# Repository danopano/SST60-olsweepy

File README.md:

# SST60-olsweepy
This repo is a fork and mod of dededecline/SST60! Below renders are from his original design.  
The provided production files cover daughterboard variants with and without flex cuts.  
Kicad 8.0 is recommended, with the JLC PCB plugin installed.  

## Fully open source multi-layout 60% PCB

<sub> renders outdated, using the old outline. </sub>

## Layout support

## Features
- RGB Underglow
- RP2040 processor
- MX and Alps compatible
- Indicator light positions for Caps Lock and Esc
- Standard tray mount support
- Gummy O-Ring support (Bakenko, ogre, etc. anything that h60 supports, this does too.)
- USB-C or Unified Daughterboard (or equivalent with the same pinout)
- Overcurrent and ESD protection
- Flex meme cuts

## ***DISCLAIMER***
Note: the below claim is not yet applicable for this fork.
This PCB has been tested and confirmed to work properly. The members of the PCB development team are not liable if you end up with a non-functional pcb. Order at your own risk. Support will not be provided but pull requests will be reviewed and possibly accepted.

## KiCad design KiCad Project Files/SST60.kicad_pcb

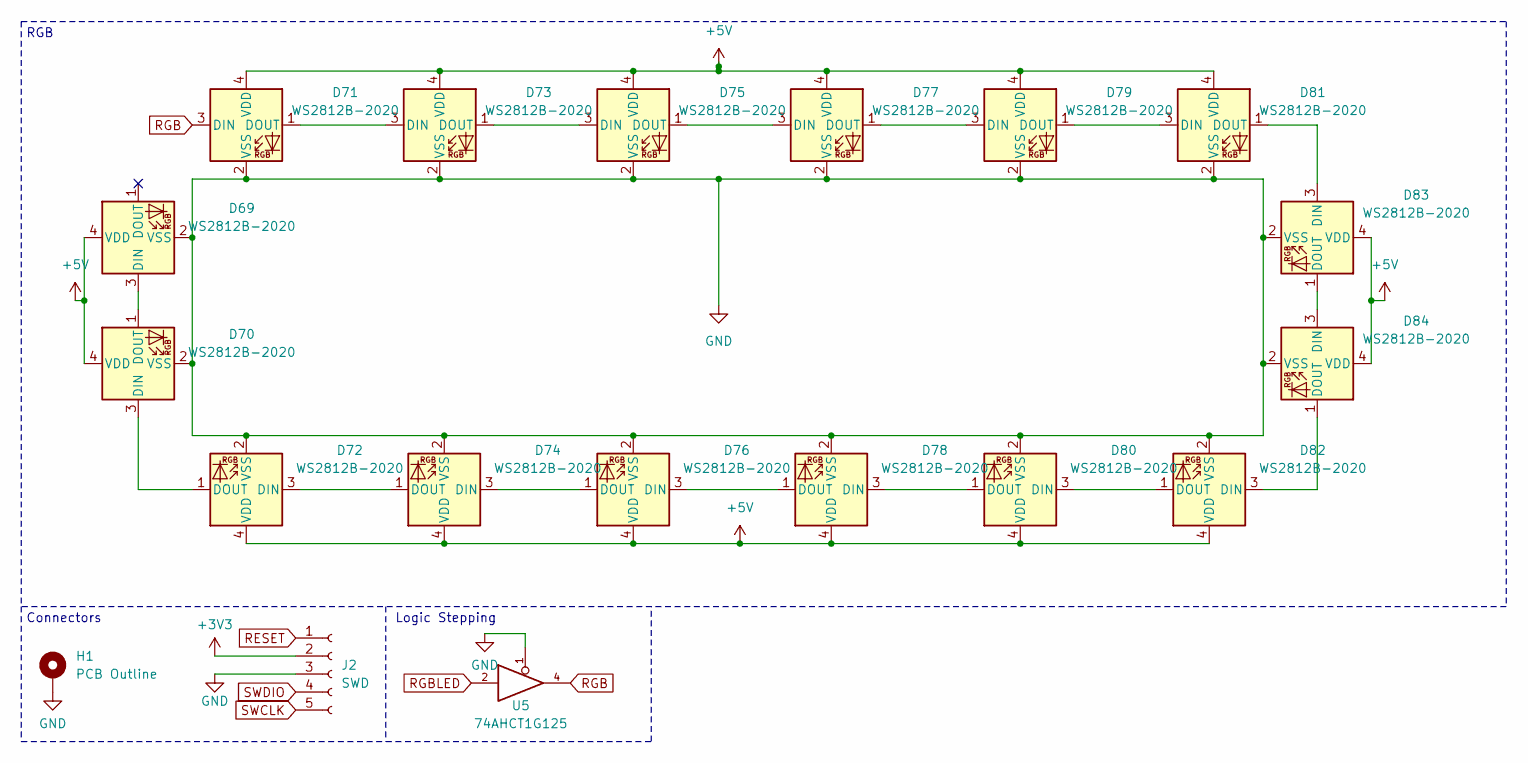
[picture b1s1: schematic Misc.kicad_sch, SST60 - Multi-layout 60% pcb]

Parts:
D69, D70, D71, D72, D73, D74, D75, D76, D77, D78, D79, D80, D81, D82, D83, D84: WS2812B-2020; LED_WS2812_2020
H1: PCB Outline; L60 Outline
J2: SWD; PinHeader_1x05_P2.54mm_Vertical
U5: 74AHCT1G125; SOT-23-5

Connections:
+3V3: J2.2; also elsewhere on the board
+5V: D69.4 (VDD), D70.4 (VDD), D71.4 (VDD), D72.4 (VDD), D73.4 (VDD), D74.4 (VDD), D75.4 (VDD), D76.4 (VDD), D77.4 (VDD), D78.4 (VDD), D79.4 (VDD), D80.4 (VDD), D81.4 (VDD), D82.4 (VDD), D83.4 (VDD), D84.4 (VDD), U5.5 (+5V); also elsewhere on the board
GND: D69.2 (VSS), D70.2 (VSS), D71.2 (VSS), D72.2 (VSS), D73.2 (VSS), D74.2 (VSS), D75.2 (VSS), D76.2 (VSS), D77.2 (VSS), D78.2 (VSS), D79.2 (VSS), D80.2 (VSS), D81.2 (VSS), D82.2 (VSS), D83.2 (VSS), D84.2 (VSS), H1.1, J2.3, U5.1, U5.3 (GND); also elsewhere on the board
unnamed: D69.3 (DIN), D70.1 (DOUT)
unnamed: D70.3 (DIN), D72.1 (DOUT)
unnamed: D71.1 (DOUT), D73.3 (DIN)
unnamed: D72.3 (DIN), D74.1 (DOUT)
unnamed: D73.1 (DOUT), D75.3 (DIN)
unnamed: D74.3 (DIN), D76.1 (DOUT)
unnamed: D75.1 (DOUT), D77.3 (DIN)
unnamed: D76.3 (DIN), D78.1 (DOUT)
unnamed: D77.1 (DOUT), D79.3 (DIN)
unnamed: D78.3 (DIN), D80.1 (DOUT)
unnamed: D79.1 (DOUT), D81.3 (DIN)
unnamed: D80.3 (DIN), D82.1 (DOUT)
unnamed: D81.1 (DOUT), D83.3 (DIN)
unnamed: D82.3 (DIN), D84.1 (DOUT)
unnamed: D83.1 (DOUT), D84.3 (DIN)
RESET: J2.1; also elsewhere on the board
RGB: D71.3 (DIN), U5.4
RGBLED: U5.2; also elsewhere on the board
SWCLK: J2.5; also elsewhere on the board
SWDIO: J2.4; also elsewhere on the board

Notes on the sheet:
Logic Stepping
Connectors
RGB

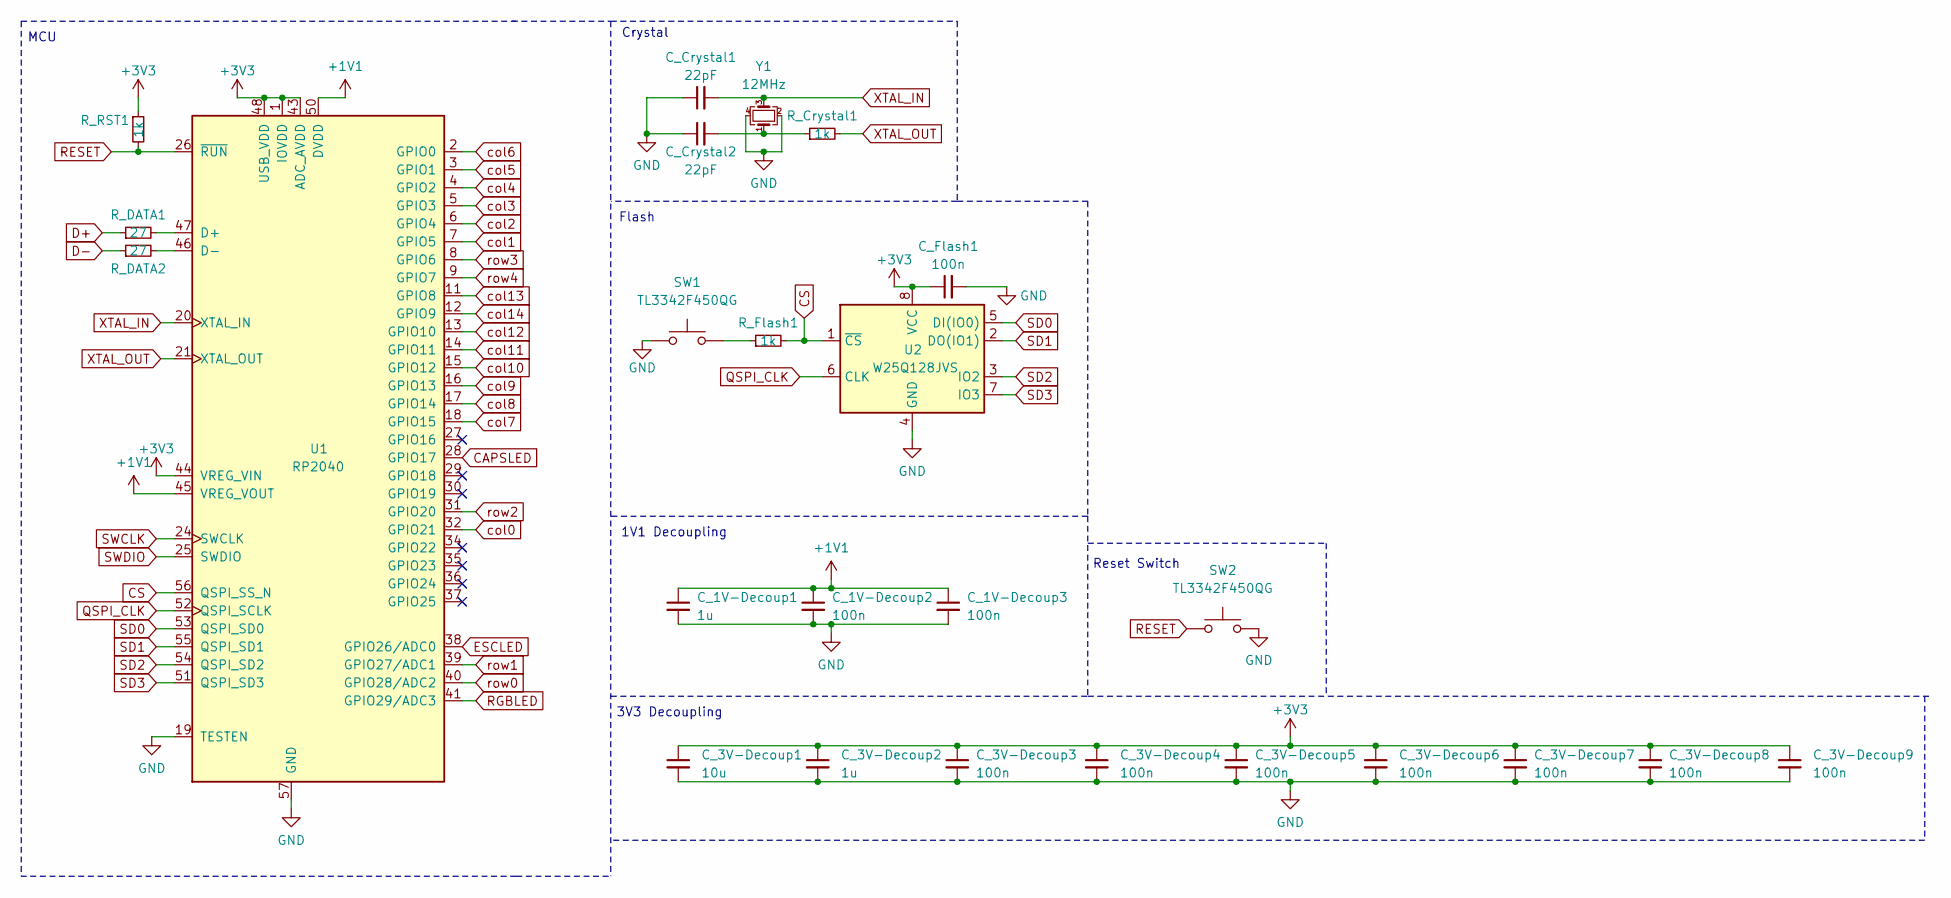
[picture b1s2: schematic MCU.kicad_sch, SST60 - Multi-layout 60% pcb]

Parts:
C_1V-Decoup1, C_3V-Decoup2: 1u; C_0402_1005Metric
C_1V-Decoup2, C_1V-Decoup3, C_3V-Decoup3, C_3V-Decoup4, C_3V-Decoup5, C_3V-Decoup6, C_3V-Decoup7, C_3V-Decoup8, C_3V-Decoup9: 100n; C_0402_1005Metric
C_3V-Decoup1: 10u; C_0402_1005Metric
C_Crystal1, C_Crystal2: 22pF; C_0402_1005Metric
C_Flash1: 100n; C_0402_1005Metric
R_Crystal1: 1k; R_0402_1005Metric
R_DATA1, R_DATA2: 27; R_0402_1005Metric
R_Flash1: 1k; R_0402_1005Metric
R_RST1: 1k; R_0402_1005Metric
SW1, SW2: TL3342F450QG; SW_SPST_TL3342
U1: RP2040; RP2040-QFN-56
U2: W25Q128JVS; SOIC-8_5.23x5.23mm_P1.27mm
Y1: 12MHz; Crystal_SMD_3225-4Pin_3.2x2.5mm

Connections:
+1V1: C_1V-Decoup1.1, C_1V-Decoup2.1, C_1V-Decoup3.1, U1.23 (DVDD), U1.45 (VREG_VOUT), U1.50 (DVDD)
+3V3: C_3V-Decoup1.1, C_3V-Decoup2.1, C_3V-Decoup3.1, C_3V-Decoup4.1, C_3V-Decoup5.1, C_3V-Decoup6.1, C_3V-Decoup7.1, C_3V-Decoup8.1, C_3V-Decoup9.1, C_Flash1.1, R_RST1.1, U1.1 (IOVDD), U1.10 (IOVDD), U1.22 (IOVDD), U1.33 (IOVDD), U1.42 (IOVDD), U1.43 (ADC_AVDD), U1.44 (VREG_VIN), U1.48 (USB_VDD), U1.49 (IOVDD), U2.8 (VCC); also elsewhere on the board
CAPSLED: U1.28 (GPIO17); also elsewhere on the board
CS: R_Flash1.2, U1.56 (QSPI_SS_N), U2.1 (~CS)
D+: R_DATA1.1; also elsewhere on the board
D-: R_DATA2.1; also elsewhere on the board
ESCLED: U1.38 (GPIO26/ADC0); also elsewhere on the board
GND: C_1V-Decoup1.2, C_1V-Decoup2.2, C_1V-Decoup3.2, C_3V-Decoup1.2, C_3V-Decoup2.2, C_3V-Decoup3.2, C_3V-Decoup4.2, C_3V-Decoup5.2, C_3V-Decoup6.2, C_3V-Decoup7.2, C_3V-Decoup8.2, C_3V-Decoup9.2, C_Crystal1.1, C_Crystal2.1, C_Flash1.2, SW1.1, SW2.2, U1.19 (TESTEN), U1.57 (GND), U2.4 (GND), Y1.2, Y1.4; also elsewhere on the board
unnamed: C_Crystal2.2, R_Crystal1.1, Y1.1
unnamed: R_Flash1.1, SW1.2
unnamed: R_DATA1.2, U1.47 (D+)
unnamed: R_DATA2.2, U1.46 (D-)
QSPI_CLK: U1.52 (QSPI_SCLK), U2.6 (CLK)
RESET: R_RST1.2, SW2.1, U1.26 (~RUN); also elsewhere on the board
RGBLED: U1.41 (GPIO29/ADC3); also elsewhere on the board
SD0: U1.53 (QSPI_SD0), U2.5 (DI(IO0))
SD1: U1.55 (QSPI_SD1), U2.2 (DO(IO1))
SD2: U1.54 (QSPI_SD2), U2.3 (IO2)
SD3: U1.51 (QSPI_SD3), U2.7 (IO3)
SWCLK: U1.24 (SWCLK); also elsewhere on the board
SWDIO: U1.25 (SWDIO); also elsewhere on the board
XTAL_IN: C_Crystal1.2, U1.20 (XTAL_IN), Y1.3
XTAL_OUT: R_Crystal1.2, U1.21 (XTAL_OUT)
col0: U1.32 (GPIO21); also elsewhere on the board
col1: U1.7 (GPIO5); also elsewhere on the board
col2: U1.6 (GPIO4); also elsewhere on the board
col3: U1.5 (GPIO3); also elsewhere on the board
col4: U1.4 (GPIO2); also elsewhere on the board
col5: U1.3 (GPIO1); also elsewhere on the board
col6: U1.2 (GPIO0); also elsewhere on the board
col7: U1.18 (GPIO15); also elsewhere on the board
col8: U1.17 (GPIO14); also elsewhere on the board
col9: U1.16 (GPIO13); also elsewhere on the board
col10: U1.15 (GPIO12); also elsewhere on the board
col11: U1.14 (GPIO11); also elsewhere on the board
col12: U1.13 (GPIO10); also elsewhere on the board
col13: U1.11 (GPIO8); also elsewhere on the board
col14: U1.12 (GPIO9); also elsewhere on the board
row0: U1.40 (GPIO28/ADC2); also elsewhere on the board
row1: U1.39 (GPIO27/ADC1); also elsewhere on the board
row2: U1.31 (GPIO20); also elsewhere on the board
row3: U1.8 (GPIO6); also elsewhere on the board
row4: U1.9 (GPIO7); also elsewhere on the board

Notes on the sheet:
Reset Switch
Flash
MCU
Crystal
3V3 Decoupling
1V1 Decoupling

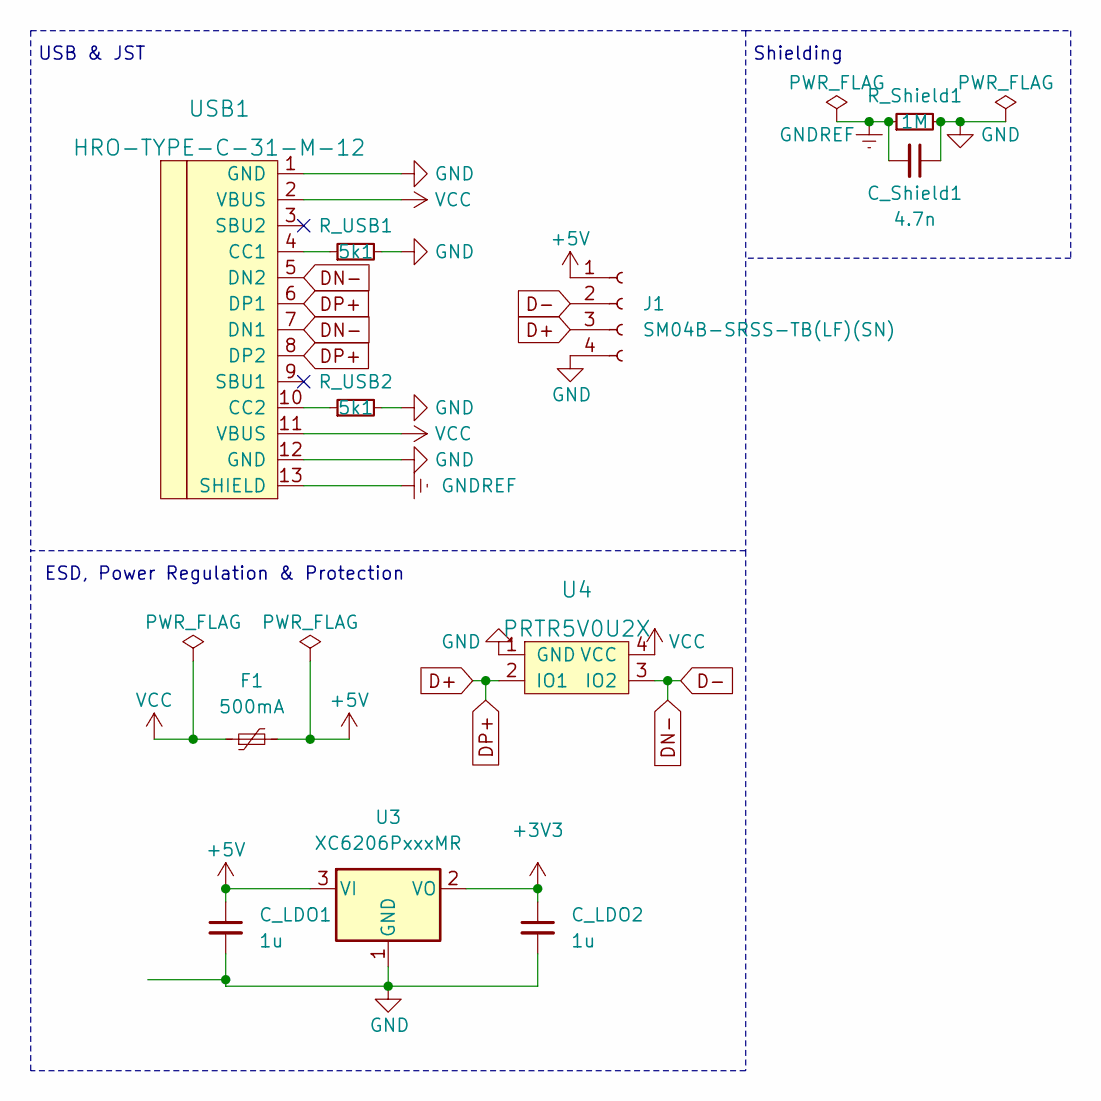
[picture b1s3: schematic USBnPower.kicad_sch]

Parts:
C_LDO1, C_LDO2: 1u; C_0402_1005Metric
C_Shield1: 4.7n; C_0402_1005Metric
F1: 500mA; Fuse_0805_2012Metric
J1: SM04B-SRSS-TB(LF)(SN); JST_SH_SM04B-SRSS-TB_1x04-1MP_P1.00mm_Horizontal
R_Shield1: 1M; R_0402_1005Metric
R_USB1, R_USB2: 5k1; R_0402_1005Metric
U3: XC6206PxxxMR; SOT-23
U4: PRTR5V0U2X; SOT143B
USB1: HRO-TYPE-C-31-M-12; HRO-TYPE-C-31-M-12-Assembly

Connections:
+3V3: C_LDO2.1, U3.2 (VO); also elsewhere on the board
+5V: C_LDO1.1, F1.2, J1.1, U3.3 (VI); also elsewhere on the board
D+: J1.3, U4.2 (IO1), USB1.6 (DP1), USB1.8 (DP2); also elsewhere on the board
D-: J1.2, U4.3 (IO2), USB1.5 (DN2), USB1.7 (DN1); also elsewhere on the board
GND: C_LDO1.2, C_LDO2.2, C_Shield1.1, J1.4, R_Shield1.2, R_USB1.2, R_USB2.2, U3.1 (GND), U4.1 (GND), USB1.1 (GND), USB1.12 (GND); also elsewhere on the board
GNDREF: C_Shield1.2, R_Shield1.1, USB1.13 (SHIELD)
unnamed: R_USB1.1, USB1.4 (CC1)
unnamed: R_USB2.1, USB1.10 (CC2)
VCC: F1.1, U4.4 (VCC), USB1.2 (VBUS), USB1.11 (VBUS)

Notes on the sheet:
Shielding
ESD, Power Regulation & Protection
USB & JST

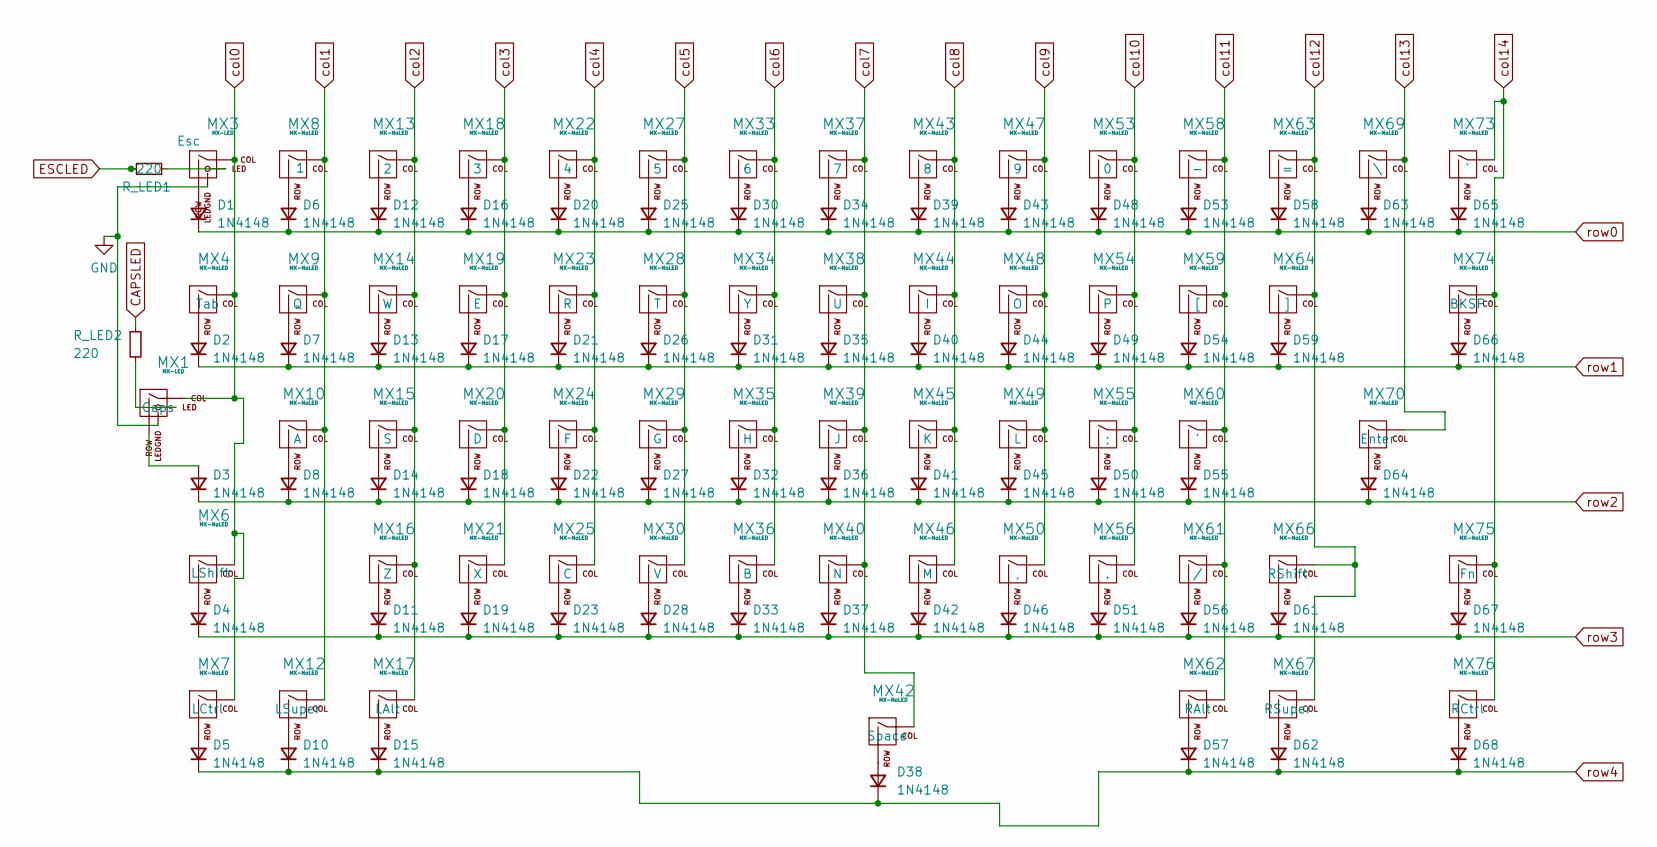
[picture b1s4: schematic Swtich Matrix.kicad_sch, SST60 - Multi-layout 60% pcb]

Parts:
D1, D2, D3, D4, D5, D6, D7, D8, D10, D11, D12, D13, D14, D15, D16, D17, D18, D19, D20, D21, D22, D23, D25, D26, D27, D28, D30, D31, D32, D33, D34, D35, D36, D37, D38, D39, D40, D41, D42, D43, D44, D45, D46, D48, D49, D50, D51, D53, D54, D55, D56, D57, D58, D59, D61, D62, D63, D64, D65, D66, D67, D68: 1N4148; D_SOD-123
MX1: MX-LED; MXOnly-1.25U
MX3: MX-LED; MXOnly-1U
MX4, MX7, MX17, MX62, MX74, MX76: MX-NoLED; MXOnly-1.5U-NoLED
MX6, MX70: MX-NoLED; MXOnly-2.25U-NoLED
MX8, MX9, MX10, MX12, MX13, MX14, MX15, MX16, MX18, MX19, MX20, MX21, MX22, MX23, MX24, MX25, MX27, MX28, MX29, MX30, MX33, MX34, MX35, MX36, MX37, MX38, MX39, MX40, MX43, MX44, MX45, MX46, MX47, MX48, MX49, MX50, MX53, MX54, MX55, MX56, MX58, MX59, MX60, MX61, MX63, MX64, MX67, MX69, MX73, MX75: MX-NoLED; MXOnly-1U-NoLED
MX42: MX-NoLED; MXOnly-7U-ReversedStabilizers-NoLED
MX66: MX-NoLED; MXOnly-1.75U-NoLED
R_LED1, R_LED2: 220; R_0402_1005Metric

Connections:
CAPSLED: R_LED2.1; also elsewhere on the board
ESCLED: R_LED1.1; also elsewhere on the board
GND: MX1.4 (LEDGND), MX3.4 (LEDGND); also elsewhere on the board
unnamed: D1.2 (A), MX3.2 (ROW)
unnamed: D2.2 (A), MX4.2 (ROW)
unnamed: D3.2 (A), MX1.2 (ROW)
unnamed: D4.2 (A), MX6.2 (ROW)
unnamed: D5.2 (A), MX7.2 (ROW)
unnamed: D6.2 (A), MX8.2 (ROW)
unnamed: D7.2 (A), MX9.2 (ROW)
unnamed: D8.2 (A), MX10.2 (ROW)
unnamed: D10.2 (A), MX12.2 (ROW)
unnamed: D11.2 (A), MX16.2 (ROW)
unnamed: D12.2 (A), MX13.2 (ROW)
unnamed: D13.2 (A), MX14.2 (ROW)
unnamed: D14.2 (A), MX15.2 (ROW)
unnamed: D15.2 (A), MX17.2 (ROW)
unnamed: D16.2 (A), MX18.2 (ROW)
unnamed: D17.2 (A), MX19.2 (ROW)
unnamed: D18.2 (A), MX20.2 (ROW)
unnamed: D19.2 (A), MX21.2 (ROW)
unnamed: D20.2 (A), MX22.2 (ROW)
unnamed: D21.2 (A), MX23.2 (ROW)
unnamed: D22.2 (A), MX24.2 (ROW)
unnamed: D23.2 (A), MX25.2 (ROW)
unnamed: D25.2 (A), MX27.2 (ROW)
unnamed: D26.2 (A), MX28.2 (ROW)
unnamed: D27.2 (A), MX29.2 (ROW)
unnamed: D28.2 (A), MX30.2 (ROW)
unnamed: D30.2 (A), MX33.2 (ROW)
unnamed: D31.2 (A), MX34.2 (ROW)
unnamed: D32.2 (A), MX35.2 (ROW)
unnamed: D33.2 (A), MX36.2 (ROW)
unnamed: D34.2 (A), MX37.2 (ROW)
unnamed: D35.2 (A), MX38.2 (ROW)
unnamed: D36.2 (A), MX39.2 (ROW)
unnamed: D37.2 (A), MX40.2 (ROW)
unnamed: D38.2 (A), MX42.2 (ROW)
unnamed: D39.2 (A), MX43.2 (ROW)
unnamed: D40.2 (A), MX44.2 (ROW)
unnamed: D41.2 (A), MX45.2 (ROW)
unnamed: D42.2 (A), MX46.2 (ROW)
unnamed: D43.2 (A), MX47.2 (ROW)
unnamed: D44.2 (A), MX48.2 (ROW)
unnamed: D45.2 (A), MX49.2 (ROW)
unnamed: D46.2 (A), MX50.2 (ROW)
unnamed: D48.2 (A), MX53.2 (ROW)
unnamed: D49.2 (A), MX54.2 (ROW)
unnamed: D50.2 (A), MX55.2 (ROW)
unnamed: D51.2 (A), MX56.2 (ROW)
unnamed: D53.2 (A), MX58.2 (ROW)
unnamed: D54.2 (A), MX59.2 (ROW)
unnamed: D55.2 (A), MX60.2 (ROW)
unnamed: D56.2 (A), MX61.2 (ROW)
unnamed: D57.2 (A), MX62.2 (ROW)
unnamed: D58.2 (A), MX63.2 (ROW)
unnamed: D59.2 (A), MX64.2 (ROW)
unnamed: D61.2 (A), MX66.2 (ROW)
unnamed: D62.2 (A), MX67.2 (ROW)
unnamed: D63.2 (A), MX69.2 (ROW)
unnamed: D64.2 (A), MX70.2 (ROW)
unnamed: D65.2 (A), MX73.2 (ROW)
unnamed: D66.2 (A), MX74.2 (ROW)
unnamed: D67.2 (A), MX75.2 (ROW)
unnamed: D68.2 (A), MX76.2 (ROW)
unnamed: MX1.3 (LED), R_LED2.2
unnamed: MX3.3 (LED), R_LED1.2
col0: MX1.1 (COL), MX3.1 (COL), MX4.1 (COL), MX6.1 (COL), MX7.1 (COL); also elsewhere on the board
col1: MX8.1 (COL), MX9.1 (COL), MX10.1 (COL), MX12.1 (COL); also elsewhere on the board
col2: MX13.1 (COL), MX14.1 (COL), MX15.1 (COL), MX16.1 (COL), MX17.1 (COL); also elsewhere on the board
col3: MX18.1 (COL), MX19.1 (COL), MX20.1 (COL), MX21.1 (COL); also elsewhere on the board
col4: MX22.1 (COL), MX23.1 (COL), MX24.1 (COL), MX25.1 (COL); also elsewhere on the board
col5: MX27.1 (COL), MX28.1 (COL), MX29.1 (COL), MX30.1 (COL); also elsewhere on the board
col6: MX33.1 (COL), MX34.1 (COL), MX35.1 (COL), MX36.1 (COL); also elsewhere on the board
col7: MX37.1 (COL), MX38.1 (COL), MX39.1 (COL), MX40.1 (COL), MX42.1 (COL); also elsewhere on the board
col8: MX43.1 (COL), MX44.1 (COL), MX45.1 (COL), MX46.1 (COL); also elsewhere on the board
col9: MX47.1 (COL), MX48.1 (COL), MX49.1 (COL), MX50.1 (COL); also elsewhere on the board
col10: MX53.1 (COL), MX54.1 (COL), MX55.1 (COL), MX56.1 (COL); also elsewhere on the board
col11: MX58.1 (COL), MX59.1 (COL), MX60.1 (COL), MX61.1 (COL), MX62.1 (COL); also elsewhere on the board
col12: MX63.1 (COL), MX64.1 (COL), MX66.1 (COL), MX67.1 (COL); also elsewhere on the board
col13: MX69.1 (COL), MX70.1 (COL); also elsewhere on the board
col14: MX73.1 (COL), MX74.1 (COL), MX75.1 (COL), MX76.1 (COL); also elsewhere on the board
row0: D1.1 (K), D6.1 (K), D12.1 (K), D16.1 (K), D20.1 (K), D25.1 (K), D30.1 (K), D34.1 (K), D39.1 (K), D43.1 (K), D48.1 (K), D53.1 (K), D58.1 (K), D63.1 (K), D65.1 (K); also elsewhere on the board
row1: D2.1 (K), D7.1 (K), D13.1 (K), D17.1 (K), D21.1 (K), D26.1 (K), D31.1 (K), D35.1 (K), D40.1 (K), D44.1 (K), D49.1 (K), D54.1 (K), D59.1 (K), D66.1 (K); also elsewhere on the board
row2: D3.1 (K), D8.1 (K), D14.1 (K), D18.1 (K), D22.1 (K), D27.1 (K), D32.1 (K), D36.1 (K), D41.1 (K), D45.1 (K), D50.1 (K), D55.1 (K), D64.1 (K); also elsewhere on the board
row3: D4.1 (K), D11.1 (K), D19.1 (K), D23.1 (K), D28.1 (K), D33.1 (K), D37.1 (K), D42.1 (K), D46.1 (K), D51.1 (K), D56.1 (K), D61.1 (K), D67.1 (K); also elsewhere on the board
row4: D5.1 (K), D10.1 (K), D15.1 (K), D38.1 (K), D57.1 (K), D62.1 (K), D68.1 (K); also elsewhere on the board

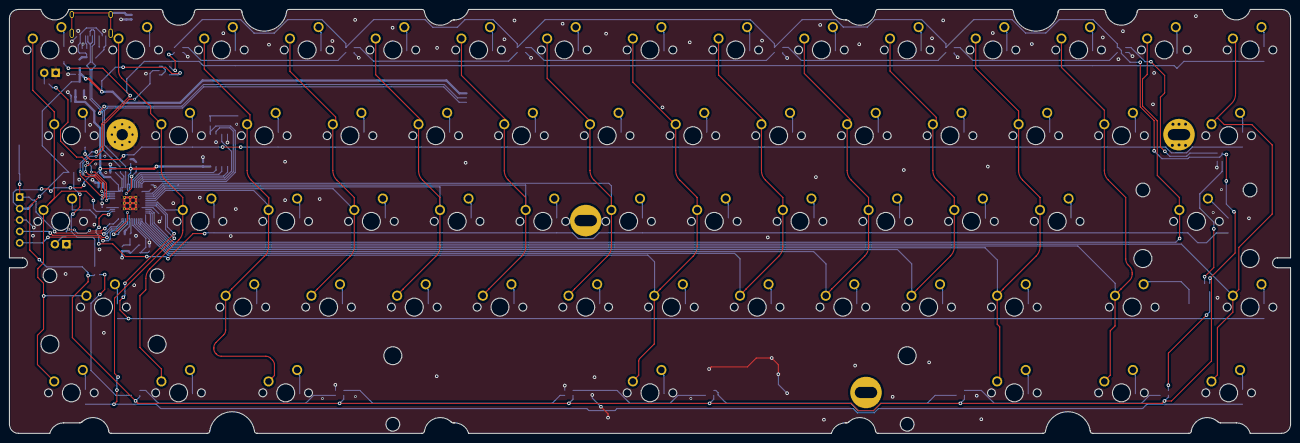
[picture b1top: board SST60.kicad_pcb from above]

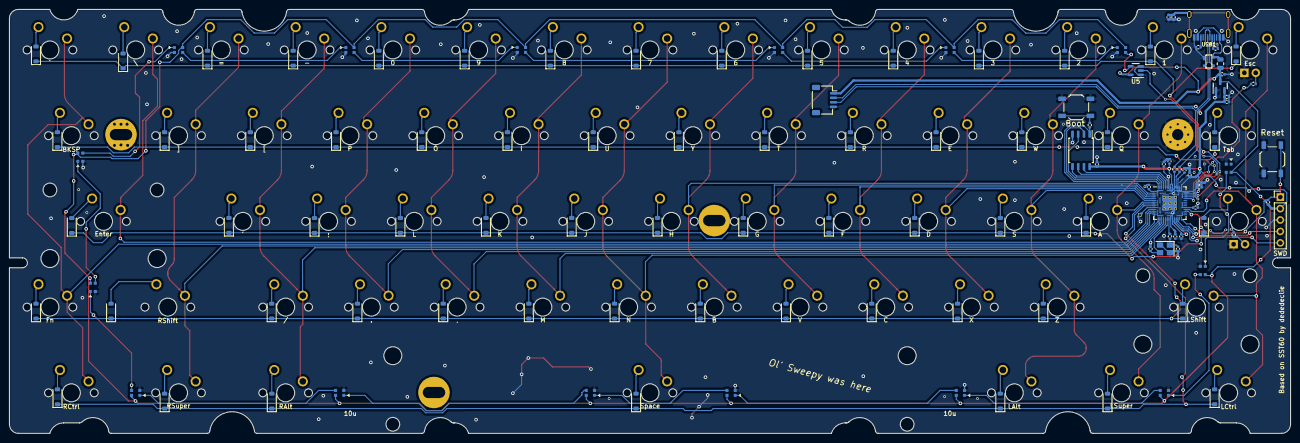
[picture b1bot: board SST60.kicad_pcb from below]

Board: 2 copper layers, 284.7 x 94.2 mm, 181 parts (118 on the bottom side), 128 nets.

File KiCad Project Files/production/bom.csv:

Designator,Footprint,Quantity,Value,LCSC Part #
"C_1V-Decoup1, C_3V-Decoup2, C_LDO1, C_LDO2",0402,4,1u,
"C_1V-Decoup2, C_1V-Decoup3, C_3V-Decoup3, C_3V-Decoup4, C_3V-Decoup5, C_3V-Decoup6, C_3V-Decoup7, C_3V-Decoup8, C_3V-Decoup9, C_Flash1",0402,10,100n,
C_3V-Decoup1,0402,1,10u,
"C_Crystal1, C_Crystal2",0402,2,22pF,
C_Shield1,0402,1,4.7n,
"D1, D10, D11, D12, D13, D14, D15, D16, D17, D18, D19, D2, D20, D21, D22, D23, D25, D26, D27, D28, D3, D30, D31, D32, D33, D34, D35, D36, D37, D38, D39, D4, D40, D41, D42, D43, D44, D45, D46, D48, D49, D5, D50, D51, D53, D54, D55, D56, D57, D58, D59, D6, D61, D62, D63, D64, D65, D66, D67, D68, D7, D8",D_SOD-123,62,1N4148,
"D69, D70, D71, D72, D73, D74, D75, D76, D77, D78, D79, D80, D81, D82, D83, D84",LED_WS2812_2020,16,WS2812B-2020,
F1,0805,1,500mA,
H1,L60 Outline,1,PCB Outline,
J1,JST_SH_SM04B-SRSS-TB_1x04-1MP_P1.00mm_Horizontal,1,SM04B,
J2,PinHeader_1x05_P2.54mm_Vertical,1,SWD,
"R_Crystal1, R_Flash1, R_RST1",0402,3,1k,
"R_DATA1, R_DATA2",0402,2,27,
"R_LED1, R_LED2",0402,2,220,
R_Shield1,0402,1,1M,
"R_USB1, R_USB2",0402,2,5k1,
"SW1, SW2",SW_SPST_TL3342,2,TL3342F450QG,
U1,RP2040-QFN-56,1,RP2040,
U2,SOIC-8_5.23x5.23mm_P1.27mm,1,W25Q128JVS,
U3,SOT-23,1,XC6206PxxxMR,
U4,SOT143B,1,PRTR5V0U2X,
U5,SOT-23-5,1,74AHCT1G125,
USB1,HRO-TYPE-C-31-M-12-Assembly,1,HRO-TYPE-C-31-M-12,
Y1,Crystal_SMD_3225-4Pin_3.2x2.5mm,1,12MHz,

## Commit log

2024-03-17 Initial Modifications
    Summary of changes from original SST60:
    -Removes extraneous keys, opting for ANSI-only, split right shift, split Backspace, 7U space bar, stepped caps lock.
    -Switched from MX-ANSI hybrid to MX-only
2024-03-24 Error Cleanup
    Resolved all errors in sch, and most errors in pcb, except "intentional" ones concerning H1.
    Will readdress rule changes and violations once attempting to submit to fab house.
2024-04-07 Component updates
    Updates to components to facilitate JLC PCB process.
2024-04-07 Further Component Updates
    More updating of components to decide what is and isn't included in output BOM and Placement files, as well as other component values, to smooth out wrinkles with JLC PCB process.
2024-04-07 Two sets of production files
    Made two distinct sets of production files: DaughterboardVersion-NOFlexCuts and DaughterboardVersion-WITHFlexCuts.
    Should be ready to order, once reviewed.
2024-06-03 Shifted JST
    This update shifts the JST connected to be placed similar to another reference keyboard, to accommodate a custom milled enclosure - also removes flex cuts -- this is now the default project file desi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
